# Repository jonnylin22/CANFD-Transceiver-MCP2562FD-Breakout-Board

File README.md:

# CAN-FD Transceiver MCP2562FD Breakout Board #

This board lays out the Microchip Technology MCP2562FD CAN-FD Transceiver IC onto a board to create an external breakout board style CAN physical layer for MCUs with an embedded CAN controller but no transceiever.  

Exact Reference Manufacturer Product Number: MCP2562FD-E/SN  

## Final Boards 3D Renders ##

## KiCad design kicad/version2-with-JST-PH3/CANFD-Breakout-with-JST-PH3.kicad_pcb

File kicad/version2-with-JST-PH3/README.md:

# CAN-FD Transceiver Breakout Board #  

This is a board with the same components except that it is routed to a JST-PH3 right angle horizontal connector to allow for use of JST-PH3 cables for the CAN bus

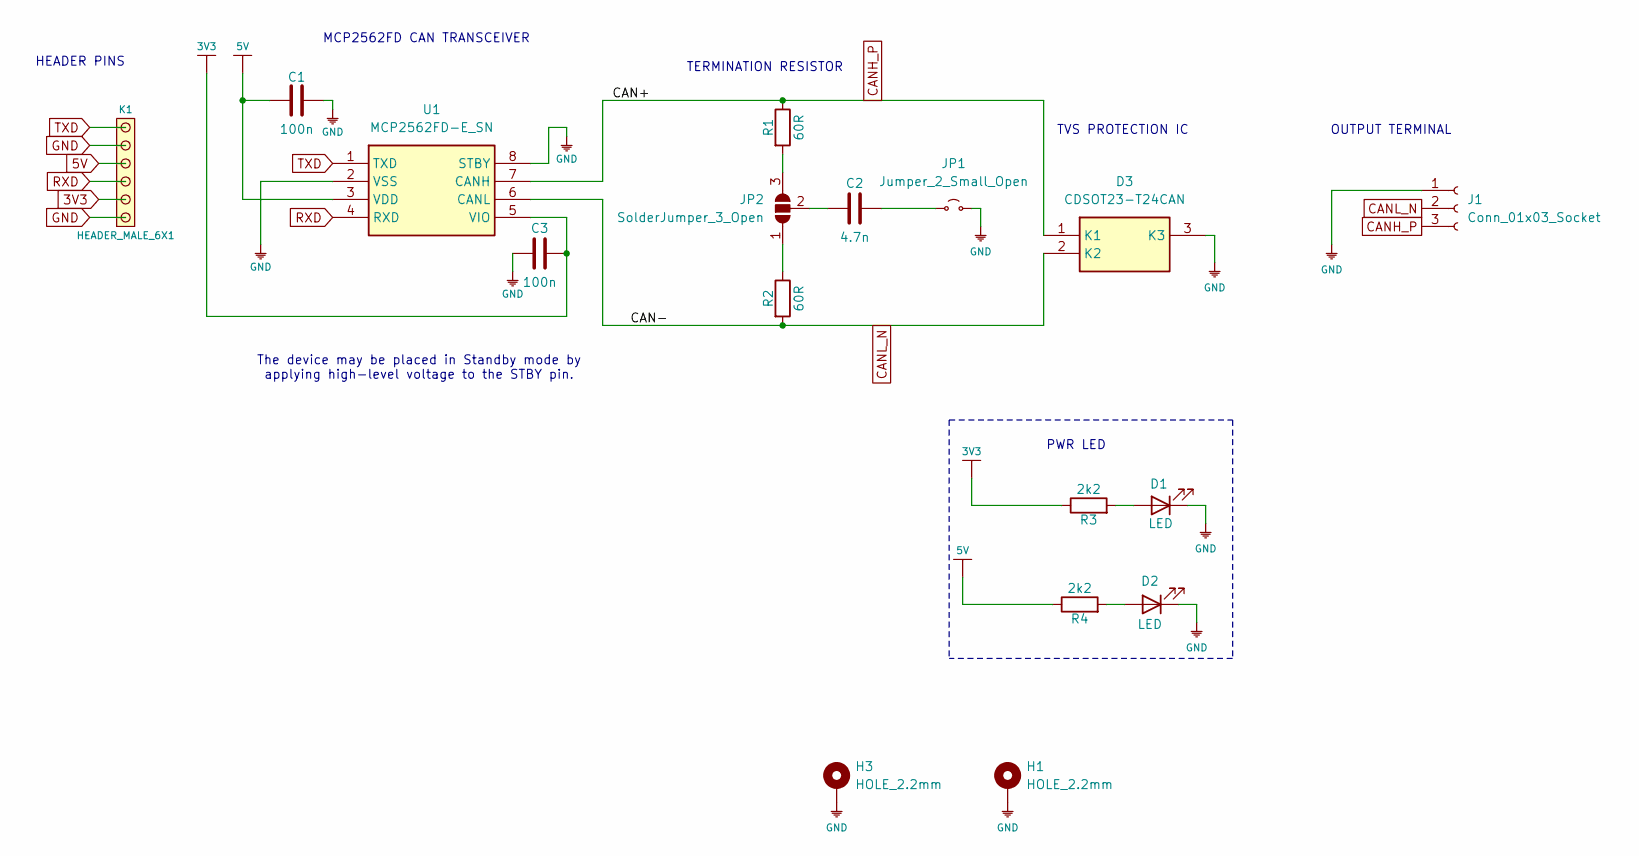
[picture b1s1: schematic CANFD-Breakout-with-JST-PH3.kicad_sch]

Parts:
C1, C3: 100n; C_0603_1608Metric_Pad1.08x0.95mm_HandSolder; Manufacturer_Part_Number CL10E104KC8VPNC; LCSC_Part_Number C16194197
C2: 4.7n; R_0402_1005Metric_Pad0.72x0.64mm_HandSolder; Manufacturer_Part_Number C0402C472J5RACTU; LCSC_Part_Number C2167398
D1, D2: LED; LED_0603_1608Metric_Pad1.05x0.95mm_HandSolder; Manufacturer_Part_Number LTST-C191KRKT; LCSC_Part_Number C125099
D3: CDSOT23-T24CAN; SOT95P230X117-3N; Mouser Part Number 652-CDSOT23-T24CAN
H1, H3: HOLE_2.2mm; MountingHole_2.2mm_M2_DIN965_Pad_TopBottom
J1: Conn_01x03_Socket; JST_PH_S3B-PH-K_1x03_P2.00mm_Horizontal
JP1: Jumper_2_Small_Open; SolderJumper-2_P1.3mm_Open_RoundedPad1.0x1.5mm
JP2: SolderJumper_3_Open; SolderJumper-3_P1.3mm_Open_Pad1.0x1.5mm_NumberLabels
K1: HEADER_MALE_6X1; PinHeader_1x06_P2.54mm_Horizontal
R1, R2: 60R; R_0402_1005Metric_Pad0.72x0.64mm_HandSolder; Manufacturer_Part_Number RC0402FR-0762RL; LCSC_Part_Number C274896
R3, R4: 2k2; R_0603_1608Metric_Pad0.98x0.95mm_HandSolder; Manufacturer_Part_Number RC0603FR-072K2L; LCSC_Part_Number C114662
U1: MCP2562FD-E_SN; SOIC127P600X175-8N; Mouser Part Number 579-MCP2562FD-E/SN

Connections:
3V3: C3.2, K1.2, R3.1, U1.5 (VIO)
5V: C1.1, K1.4, R4.1, U1.3 (VDD)
CANH_P: D3.1 (K1), J1.3, R1.1, U1.7 (CANH)
CANL_N: D3.2 (K2), J1.2, R2.2, U1.6 (CANL)
GND: C1.2, C3.1, D1.1 (K), D2.1 (K), D3.3 (K3), H1.1, H3.1, J1.1, JP1.2 (B), K1.1, K1.5, U1.2 (VSS), U1.8 (STBY)
unnamed: D1.2 (A), R3.2
unnamed: D2.2 (A), R4.2
unnamed: C2.2, JP1.1 (A)
unnamed: JP2.1 (A), R2.1
unnamed: JP2.3 (B), R1.2
unnamed: C2.1, JP2.2 (C)
RXD: K1.3, U1.4 (RXD)
TXD: K1.6, U1.1 (TXD)

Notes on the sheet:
HEADER PINS
PWR LED
OUTPUT TERMINAL
MCP2562FD CAN TRANSCEIVER
TVS PROTECTION IC
TERMINATION RESISTOR
The device may be placed in Standby mode by applying high-level voltage to the STBY pin.

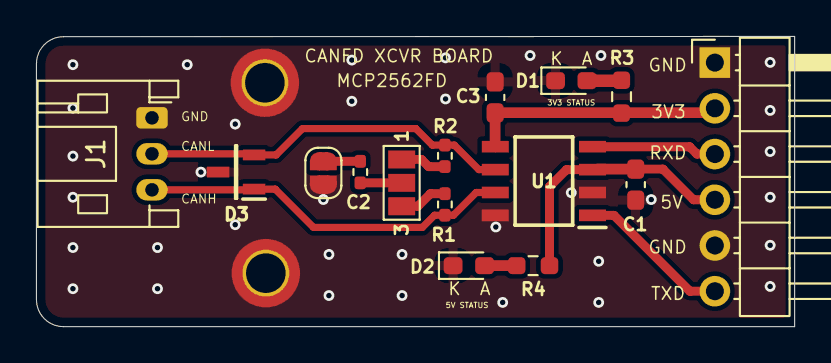
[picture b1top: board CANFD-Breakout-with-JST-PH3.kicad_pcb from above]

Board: 2 copper layers, 42.1 x 16.1 mm, 17 parts (0 on the bottom side), 13 nets.

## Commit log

2026-03-26 setting up project template
2026-03-26 moved to kicad folder
2026-03-26 editing schematic
2026-03-27 finished designing CANFD breakout
2026-03-27 edited gitignore
2026-03-27 gerber zip
2026-03-27 refine
2026-03-27 rename back
2026-03-27 final changes
2026-03-27 gerbers
2026-03-28 final revision
2026-03-28 v2 with jst connector
2026-03-28 clean up files
2026-03-28 readme for v2
2026-03-28 tracking csv files now
2026-03-28 added readmes
